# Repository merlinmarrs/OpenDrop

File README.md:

# OpenDrop
Tweaking Gaudi Labs Open Drops project for prototyping at Fablab Digiscope

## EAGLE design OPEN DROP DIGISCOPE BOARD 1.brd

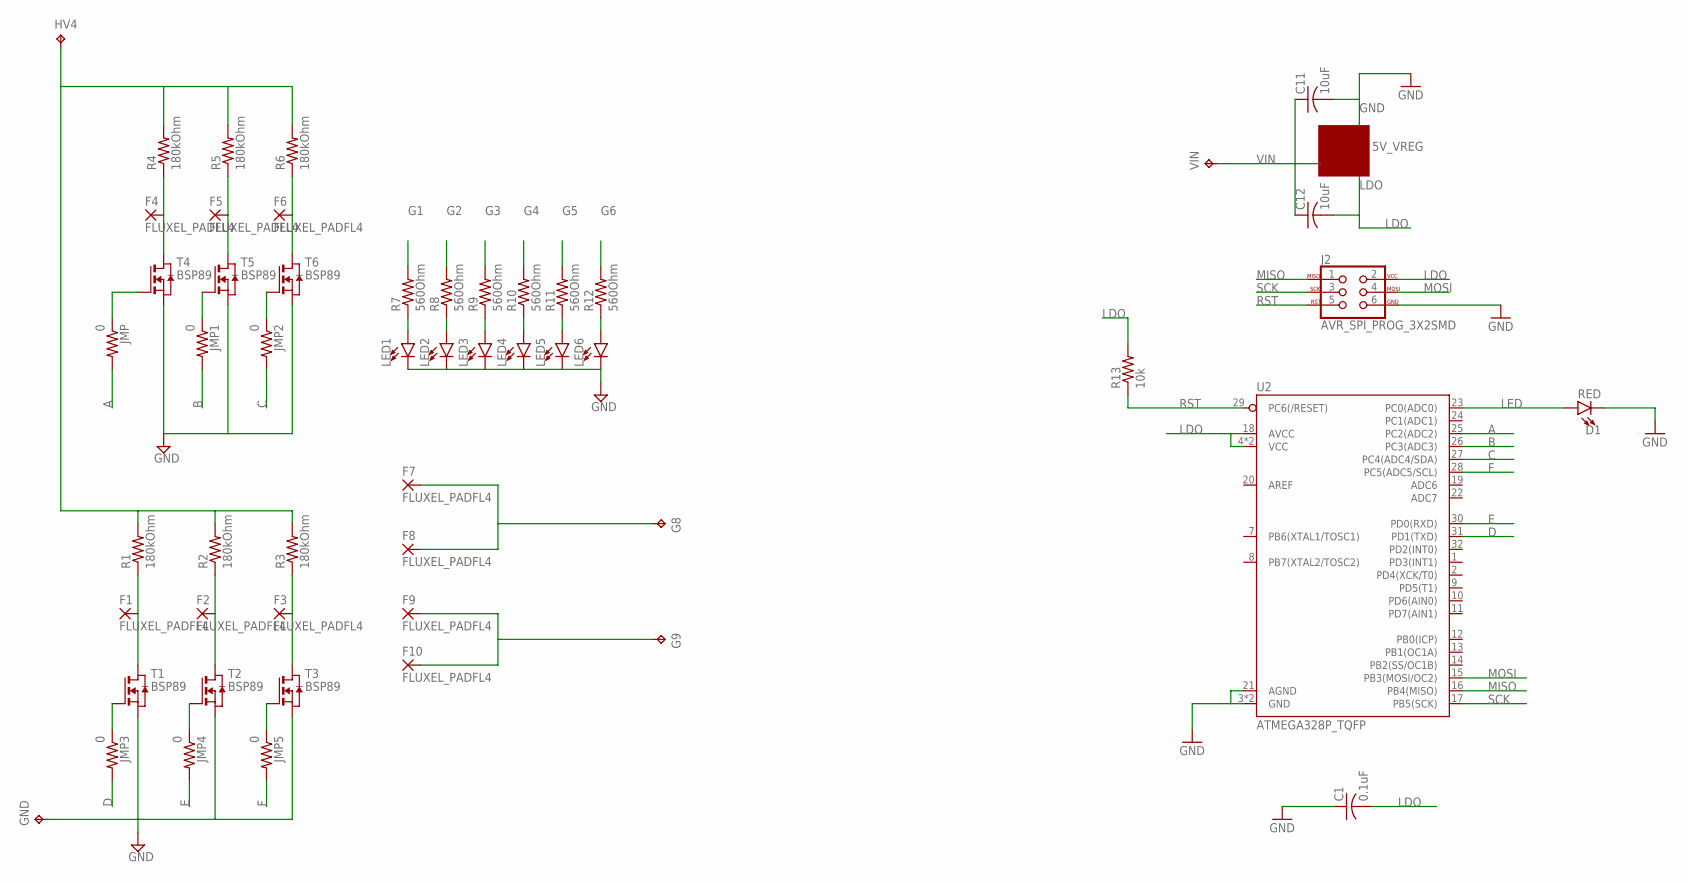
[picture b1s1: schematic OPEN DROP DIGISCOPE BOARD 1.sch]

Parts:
5V_VREG: MOSFET_PCH-DMG2305UX-7; SOT23-3
C1: 0.1uF; C1206
C11, C12: 10uF; C1206
D1: RED; LED-1206
F1, F2, F3, F4, F5, F6, F7, F8, F9, F10: FLUXEL_PADFL4; FLUXEL_PAD4
G8, G9: TPB2,54; B2,54
GND: TPB2,54; B2,54
HV4: TPB2,54; B2,54
J2: AVR_SPI_PROG_3X2SMD; 2X3_SMT_POSTS
JMP, JMP1, JMP2, JMP3, JMP4, JMP5: 0; M1206
LED1, LED2, LED3, LED4, LED5, LED6: LED1206; LED-1206
R1, R2, R3, R4, R5, R6: 180kOhm; M1206
R7, R8, R9, R10, R11, R12: 560Ohm; M1206
R13: 10k; R1206
T1, T2, T3, T4, T5, T6: BSP89; SOT223
U2: ATMEGA328P_TQFP; TQFP32-08
VIN: TPB2,54; B2,54

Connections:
A: JMP.2, U2.25 (PC2(ADC2))
B: JMP1.2, U2.26 (PC3(ADC3))
C: JMP2.2, U2.27 (PC4(ADC4/SDA))
D: JMP3.2, U2.31 (PD1(TXD))
E: JMP4.2, U2.30 (PD0(RXD))
F: JMP5.2, U2.28 (PC5(ADC5/SCL))
G1: JMP3.1, R7.2, T1.1 (G)
G2: JMP4.1, R8.2, T2.1 (G)
G3: JMP5.1, R9.2, T3.1 (G)
G4: JMP.1, R10.2, T4.1 (G)
G5: JMP1.1, R11.2, T5.1 (G)
G6: JMP2.1, R12.2, T6.1 (G)
GND: 5V_VREG.3 (D), C1.1, C11.2, D1.C, GND.TP, J2.6, LED1.C, LED2.C, LED3.C, LED4.C, LED5.C, LED6.C, T1.3 (S), T2.3 (S), T3.3 (S), T4.3 (S), T5.3 (S), T6.3 (S), U2.3 (GND), U2.5 (GND), U2.21 (AGND)
LDO: 5V_VREG.2 (S), C1.2, C12.2, J2.2, R13.2, U2.4 (VCC), U2.6 (VCC), U2.18 (AVCC)
LED: D1.A, U2.23 (PC0(ADC0))
MISO: J2.1, U2.16 (PB4(MISO))
MOSI: J2.4, U2.15 (PB3(MOSI/OC2))
unnamed: F1.1, R1.1, T1.2 (D), T1.4 (D)
unnamed: F2.1, R2.1, T2.2 (D), T2.4 (D)
unnamed: F3.1, R3.1, T3.2 (D), T3.4 (D)
unnamed: HV4.TP, R1.2, R2.2, R3.2, R4.2, R5.2, R6.2
unnamed: F6.1, R6.1, T6.2 (D), T6.4 (D)
unnamed: F5.1, R5.1, T5.2 (D), T5.4 (D)
unnamed: F4.1, R4.1, T4.2 (D), T4.4 (D)
unnamed: F7.1, F8.1, G8.TP
unnamed: F9.1, F10.1, G9.TP
unnamed: LED1.A, R7.1
unnamed: LED2.A, R8.1
unnamed: LED3.A, R9.1
unnamed: LED4.A, R10.1
unnamed: LED5.A, R11.1
unnamed: LED6.A, R12.1
RST: J2.5, R13.1, U2.29 (PC6(/RESET))
SCK: J2.3, U2.17 (PB5(SCK))
VIN: 5V_VREG.1 (G), C11.1, C12.1, VIN.TP

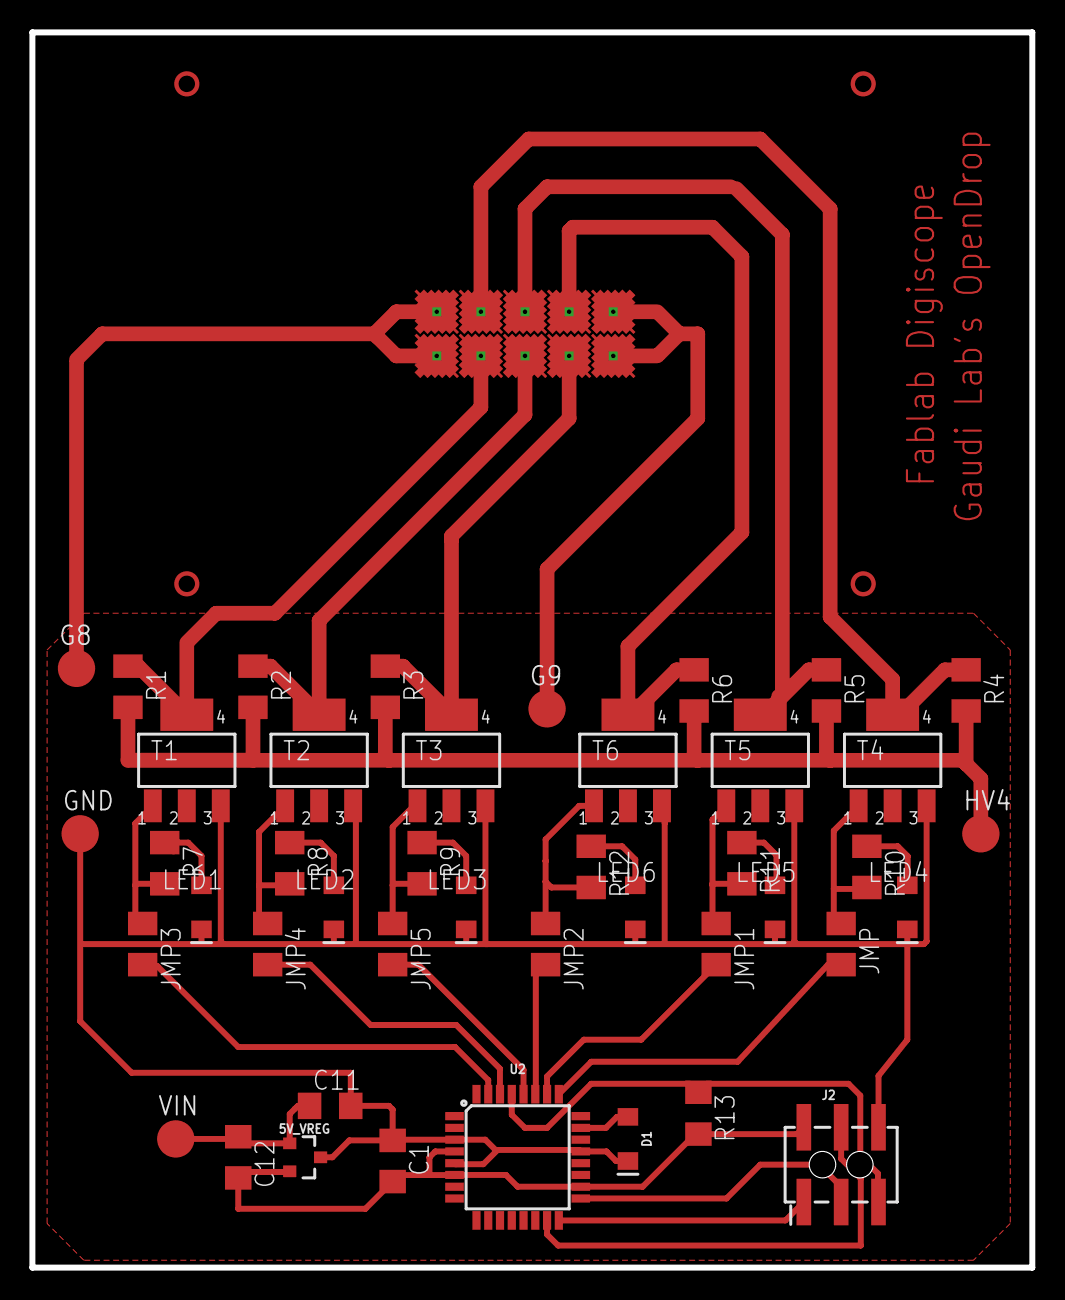
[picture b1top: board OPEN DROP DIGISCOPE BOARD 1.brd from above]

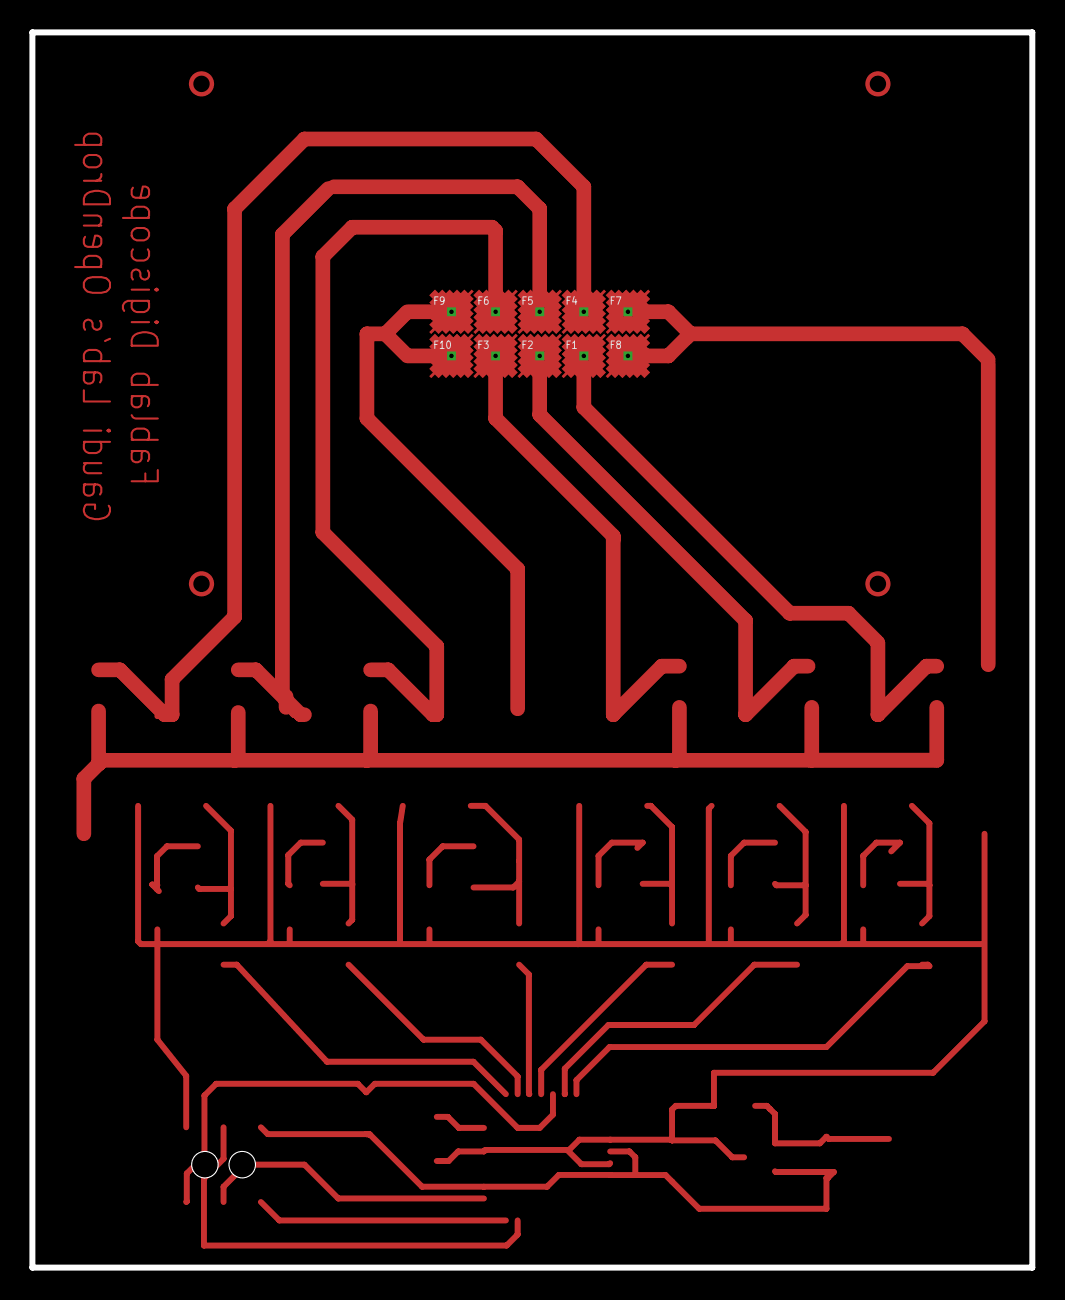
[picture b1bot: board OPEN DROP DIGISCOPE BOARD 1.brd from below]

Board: 4 copper layers, 68.0 x 84.0 mm, 53 parts (10 on the bottom side), 35 nets.

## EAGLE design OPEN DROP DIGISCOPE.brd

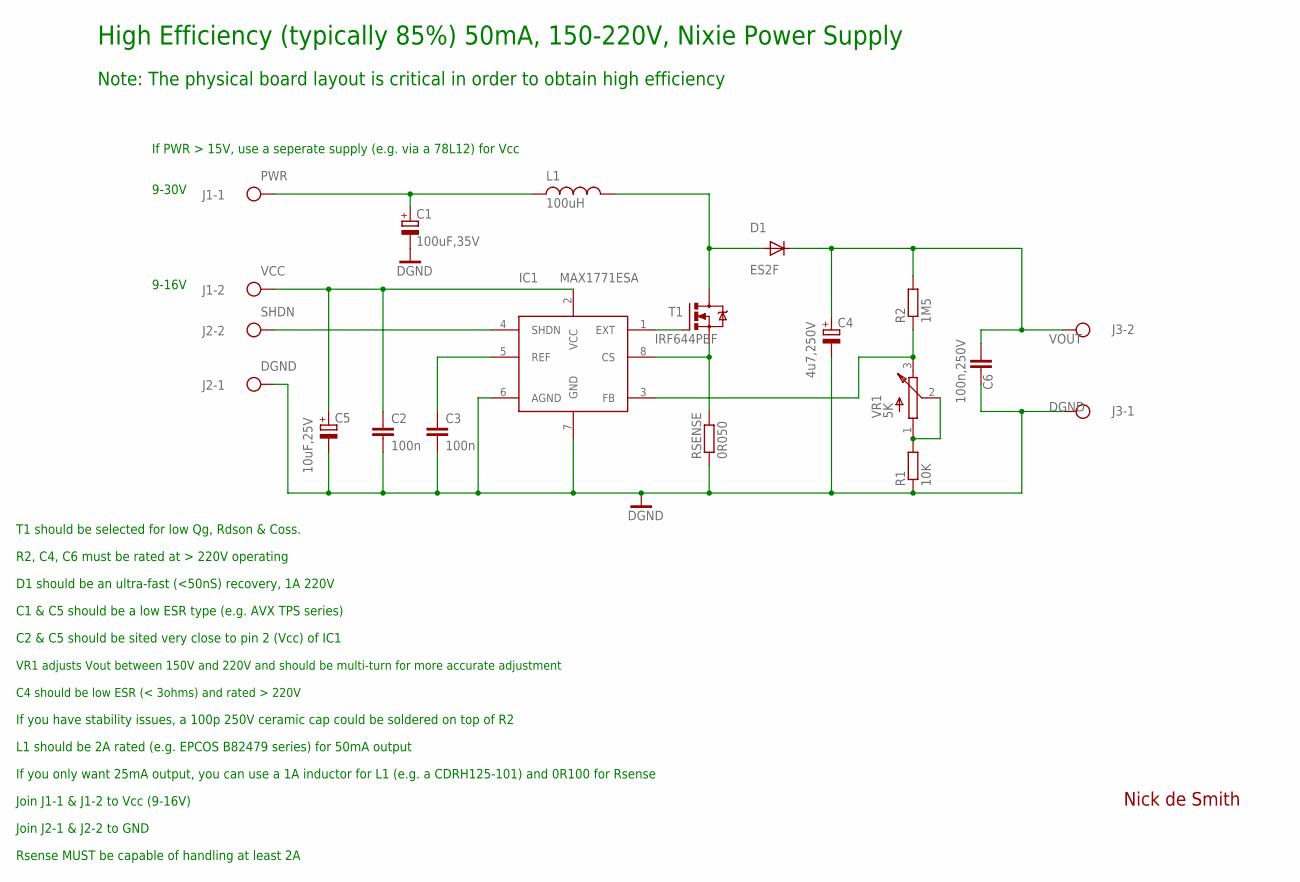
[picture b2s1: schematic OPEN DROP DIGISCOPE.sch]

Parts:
C1: 100uF,35V; C-EIA-7343
C2, C3: 100n; C0805
C4: 4u7,250V; NICHICON-UJ-12
C5: 10uF,25V; C-EIA-7343
C6: 100n,250V; C2420
D1: ES2F; SMC
IC1: MAX1771ESA; SO-8
J1, J2, J3: TERM-BLOCK-2-02IN; SCREW-2-02
L1: 100uH; L-B82479
R1: 10K; R0805
R2: 1M5; R2512
RSENSE: 0R050; R2010
T1: IRF644PBF; TO220BV
VR1: 5K; BOURNS-3214W

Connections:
DGND: C1.-, C2.2, C3.2, C4.1 (-), C5.-, C6.P$2 (2), IC1.6 (AGND), IC1.7 (GND), J2.1, J3.1, R1.1, RSENSE.1
EXT: IC1.1 (EXT), T1.G
unnamed: IC1.8 (CS), RSENSE.2, T1.S
unnamed: R1.2, VR1.1 (A), VR1.2 (W)
unnamed: IC1.3 (FB), R2.1, VR1.3 (B)
unnamed: D1.A, L1.P$2 (2), T1.D
unnamed: C3.1, IC1.5 (REF)
PWR: C1.+, J1.1, L1.P$1 (1)
SHDN: IC1.4 (SHDN), J2.2
VCC: C2.1, C5.+, IC1.2 (VCC), J1.2
VOUT: C4.2 (+), C6.P$1 (1), D1.C, J3.2, R2.2

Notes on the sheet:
R2, C4, C6 must be rated at > 220V operating
D1 should be an ultra-fast (<50nS) recovery, 1A 220V
C1 & C5 should be a low ESR type (e.g. AVX TPS series)
C2 & C5 should be sited very close to pin 2 (Vcc) of IC1
Nick de Smith
VR1 adjusts Vout between 150V and 220V and should be multi-turn for more accurate adjustment
C4 should be low ESR (< 3ohms) and rated > 220V
If you have stability issues, a 100p 250V ceramic cap could be soldered on top of R2
L1 should be 2A rated (e.g. EPCOS B82479 series) for 50mA output
Join J1-1 & J1-2 to Vcc (9-16V)
Join J2-1 & J2-2 to GND
T1 should be selected for low Qg, Rdson & Coss.
Rsense MUST be capable of handling at least 2A
High Efficiency (typically 85%) 50mA, 150-220V, Nixie Power Supply
9-16V
9-30V
If PWR > 15V, use a seperate supply (e.g. via a 78L12) for Vcc
Note: The physical board layout is critical in order to obtain high efficiency
If you only want 25mA output, you can use a 1A inductor for L1 (e.g. a CDRH125-101) and 0R100 for Rsense

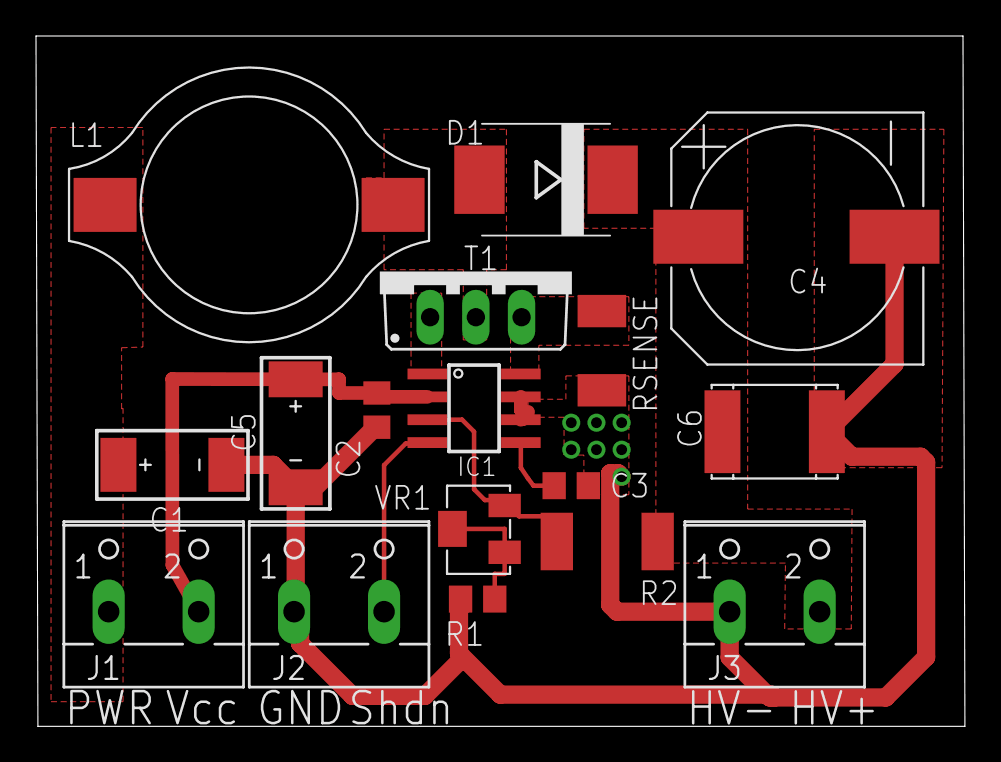
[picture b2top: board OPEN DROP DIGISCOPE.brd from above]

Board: 2 copper layers, 51.6 x 38.4 mm, 17 parts (0 on the bottom side), 11 nets.

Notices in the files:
parts and their libraries:
SparkFun-IC-Microcontroller: Licensing: Creative Commons ShareAlike 4.0 International - https://creativecommons.org/licenses/by-sa/4.0
